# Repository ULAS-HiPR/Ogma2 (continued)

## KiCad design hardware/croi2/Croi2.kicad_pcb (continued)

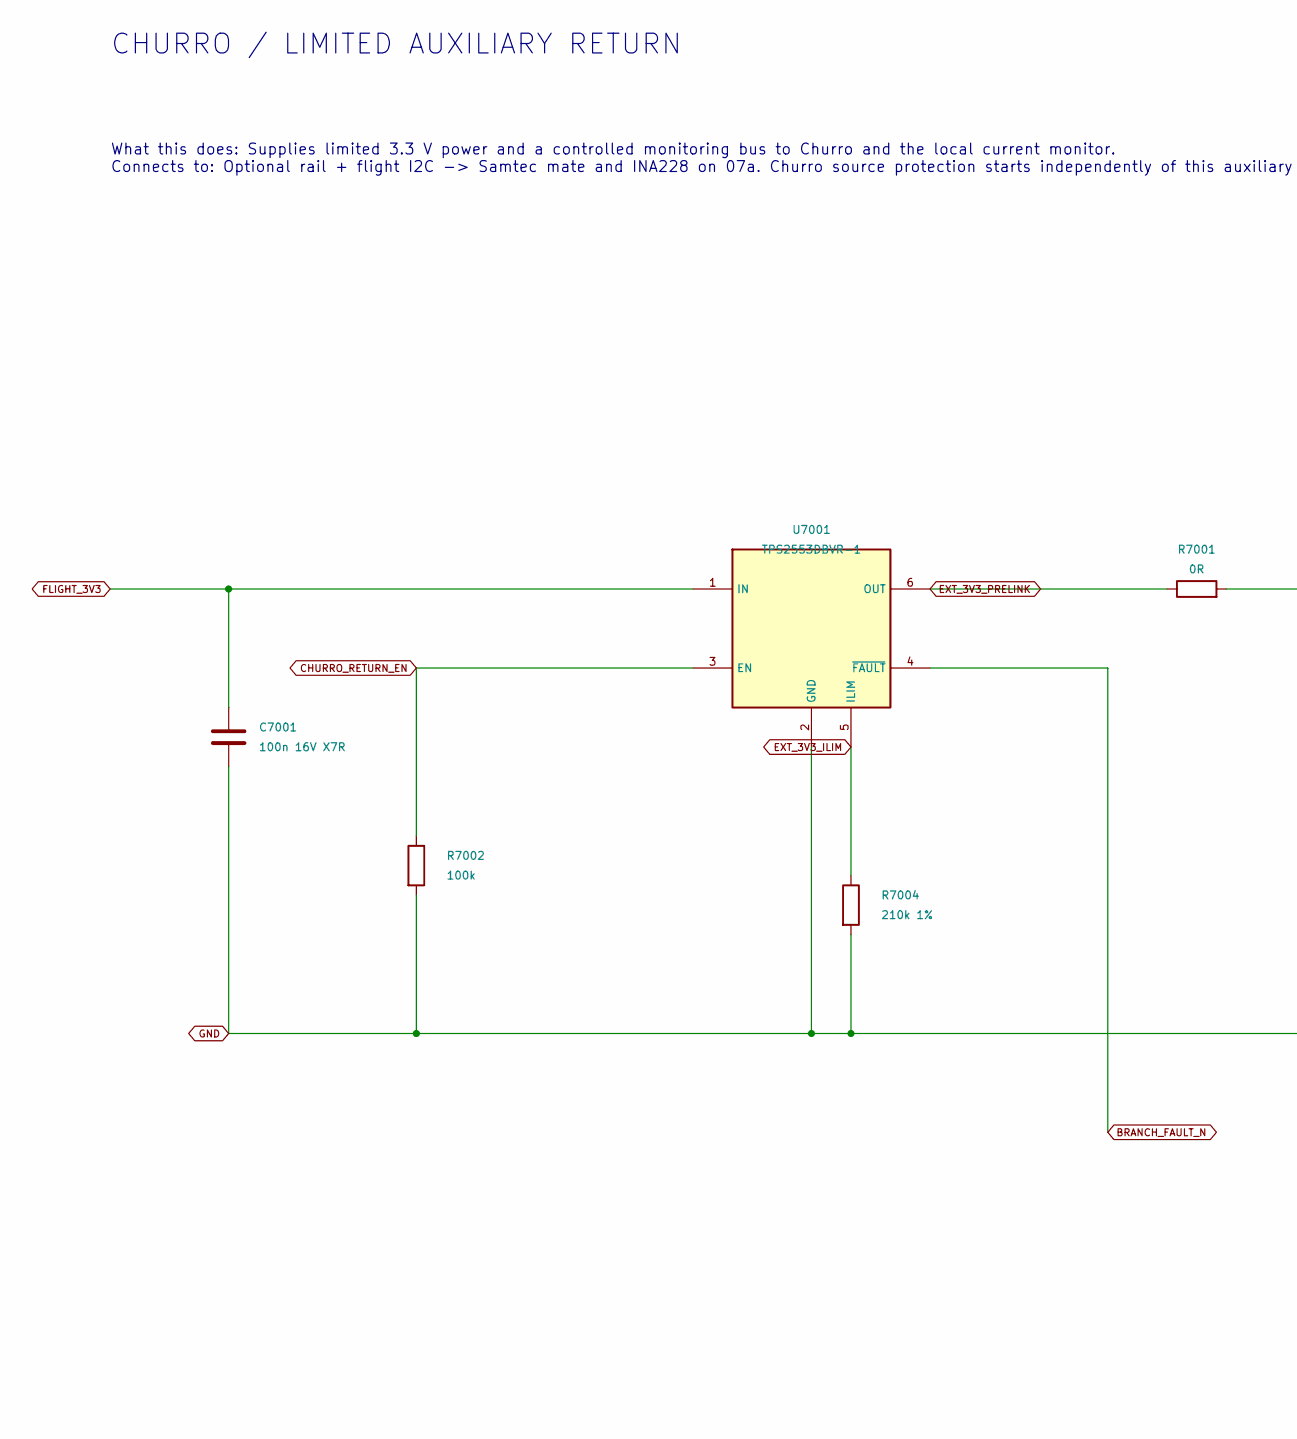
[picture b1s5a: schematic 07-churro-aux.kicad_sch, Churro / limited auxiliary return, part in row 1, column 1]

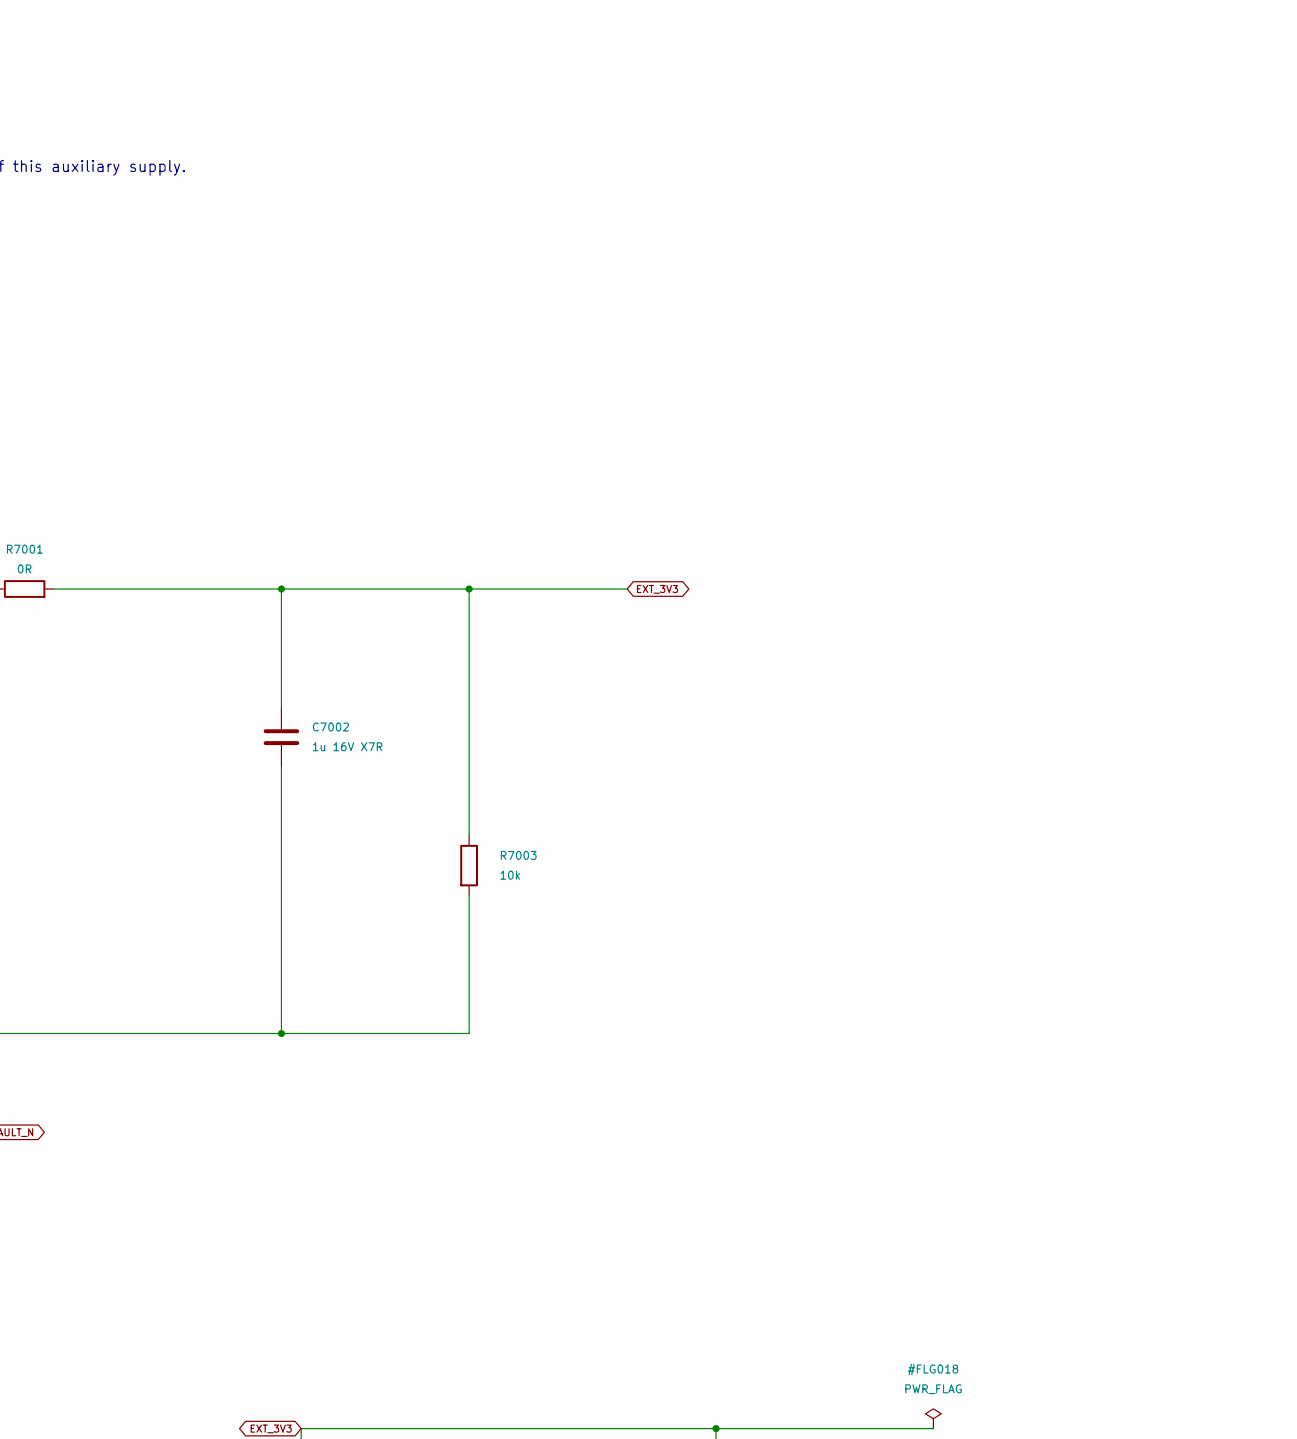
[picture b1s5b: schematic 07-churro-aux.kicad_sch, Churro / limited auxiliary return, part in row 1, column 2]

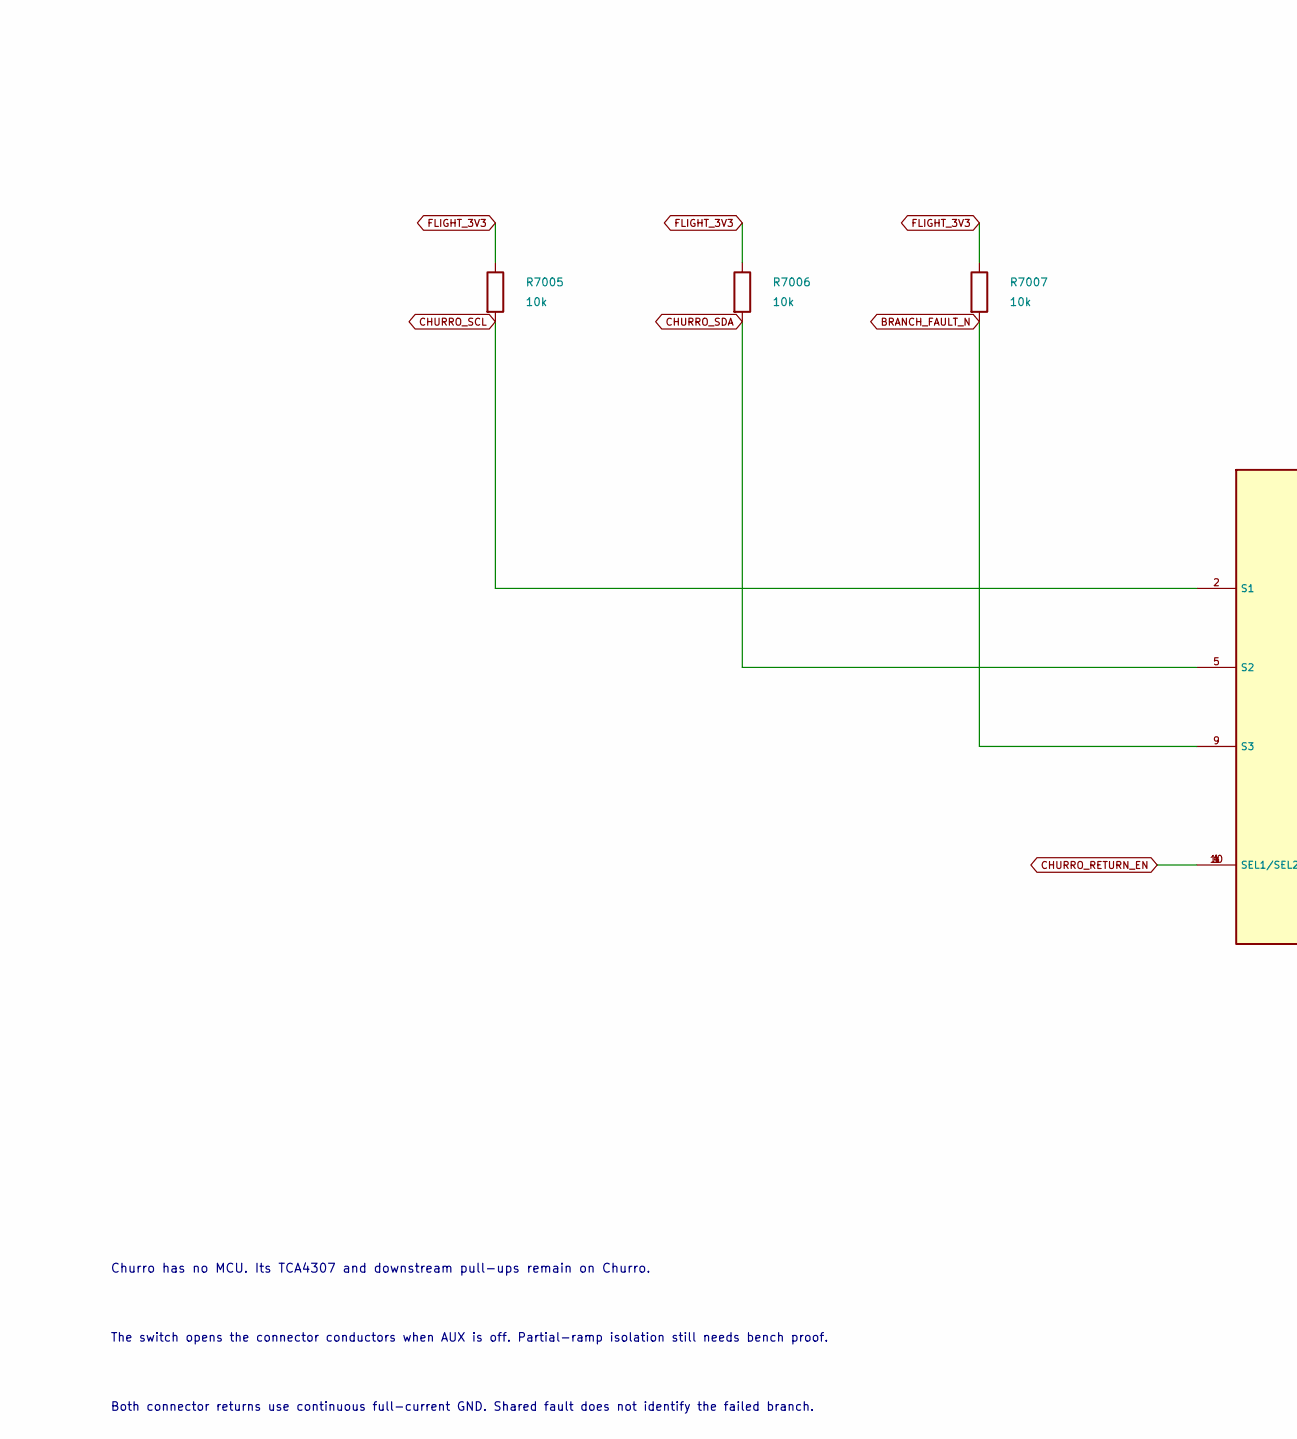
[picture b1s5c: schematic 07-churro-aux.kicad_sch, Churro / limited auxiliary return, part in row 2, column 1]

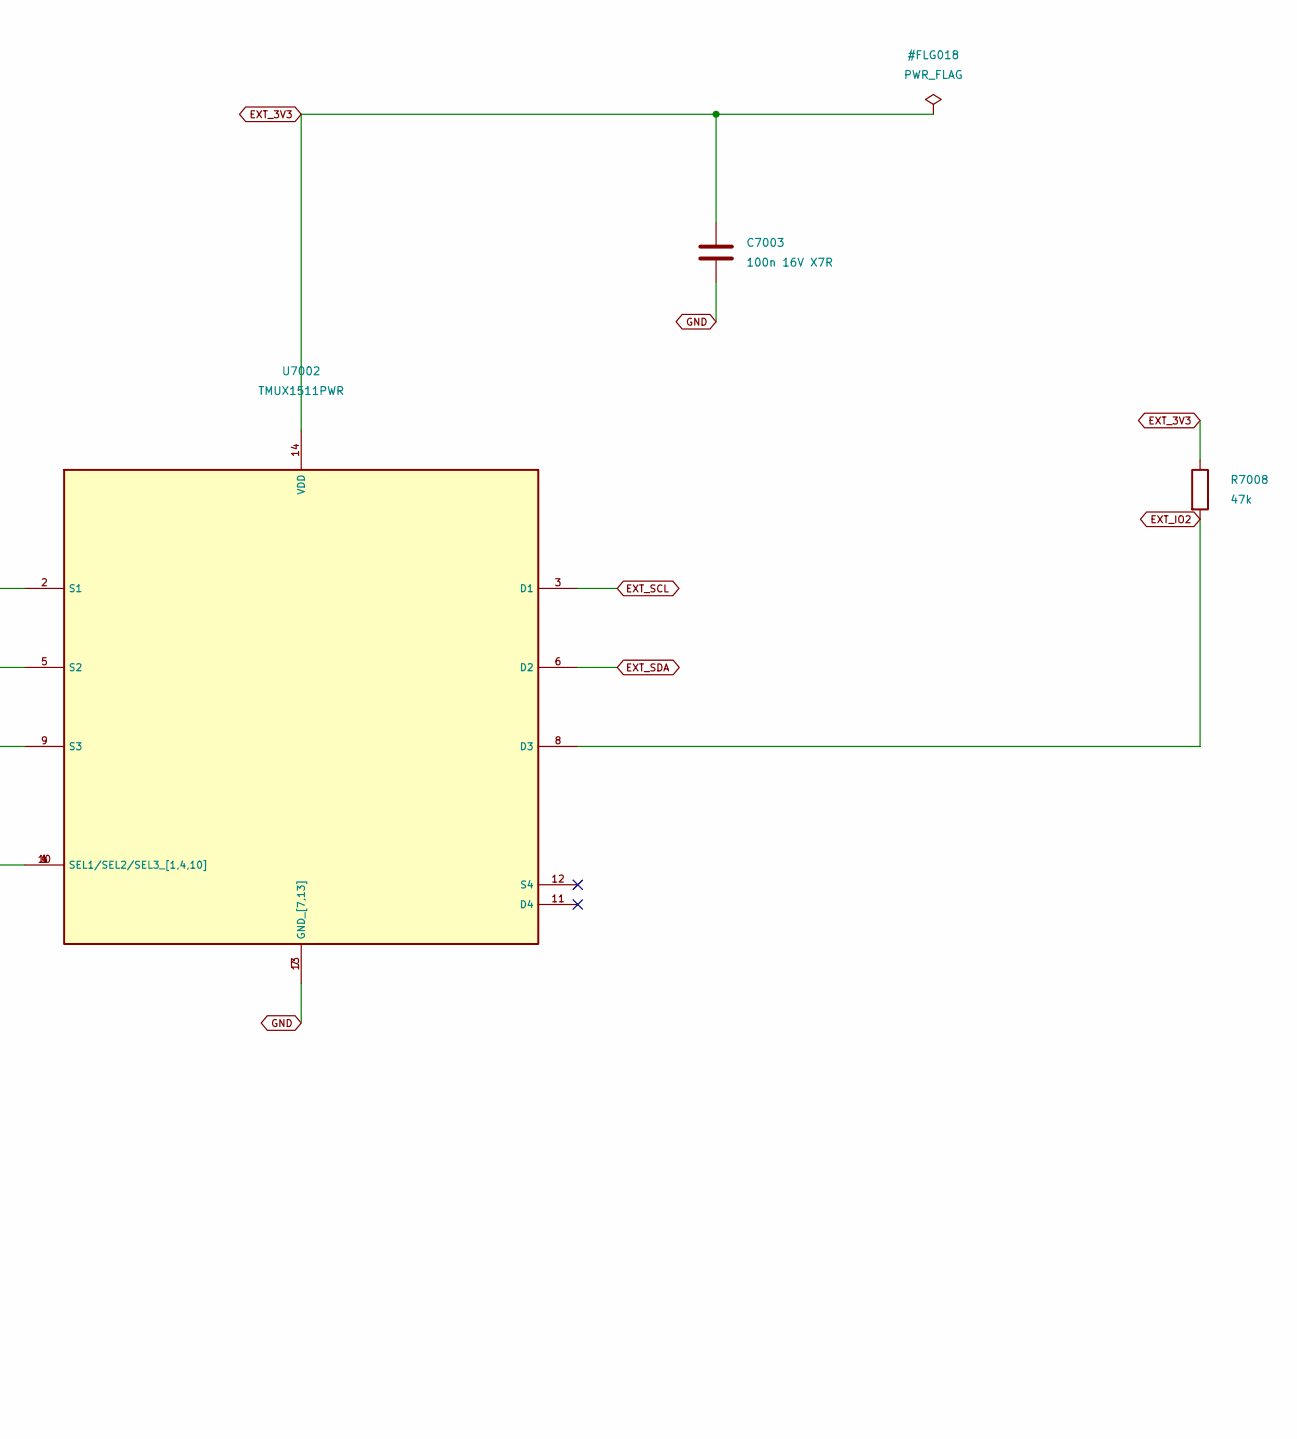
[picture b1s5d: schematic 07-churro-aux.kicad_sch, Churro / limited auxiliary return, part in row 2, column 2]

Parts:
C7001, C7003: 100n 16V X7R; C_0402_1005Metric; MPN CL05B104KB54PNC; LCSC C307331
C7002: 1u 16V X7R; C_0603_1608Metric
R7001: 0R; R_0603_1608Metric
R7002: 100k; R_0402_1005Metric; MPN 0402WGF1003TCE; LCSC C25741
R7003, R7005, R7006, R7007: 10k; R_0402_1005Metric; MPN 0402WGF1002TCE; LCSC C25744
R7004: 210k 1%; R_0603_1608Metric
R7008: 47k; R_0402_1005Metric; MPN 0402WGF4702TCE; LCSC C25792
U7001: TPS2553DBVR-1; MPN TPS2553DBVR-1
U7002: TMUX1511PWR; MPN TMUX1511PWR

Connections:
BRANCH_FAULT_N: R7007.2, U7001.4 (~FAULT), U7002.9 (S3); also elsewhere on the board
CHURRO_RETURN_EN: R7002.1, U7001.3 (EN), U7002.1 (SEL1/SEL2/SEL3_[1,4,10]), U7002.4, U7002.10; also elsewhere on the board
CHURRO_SCL: R7005.2, U7002.2 (S1); also elsewhere on the board
CHURRO_SDA: R7006.2, U7002.5 (S2); also elsewhere on the board
EXT_3V3: C7002.1, C7003.1, R7001.2, R7003.1, R7008.1, U7002.14 (VDD); also elsewhere on the board
EXT_3V3_ILIM: R7004.1, U7001.5 (ILIM)
EXT_3V3_PRELINK: R7001.1, U7001.6 (OUT)
EXT_IO2: R7008.2, U7002.8 (D3); also elsewhere on the board
EXT_SCL: U7002.3 (D1); also elsewhere on the board
EXT_SDA: U7002.6 (D2); also elsewhere on the board
FLIGHT_3V3: C7001.1, R7005.1, R7006.1, R7007.1, U7001.1 (IN); also elsewhere on the board
GND: C7001.2, C7002.2, C7003.2, R7002.2, R7003.2, R7004.2, U7001.2 (GND), U7002.7 (GND_[7,13]), U7002.13; also elsewhere on the board

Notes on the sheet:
Churro has no MCU. Its TCA4307 and downstream pull-ups remain on Churro.
CHURRO / LIMITED AUXILIARY RETURN
Both connector returns use continuous full-current GND. Shared fault does not identify the failed branch.
What this does: Supplies limited 3.3 V power and a controlled monitoring bus to Churro and the local current monitor. Connects to: Optional rail + flight I2C -> Samtec mate and INA228 on 07a. Churro source protection starts independently of this auxiliary supply.
The switch opens the connector conductors when AUX is off. Partial-ramp isolation still needs bench proof.

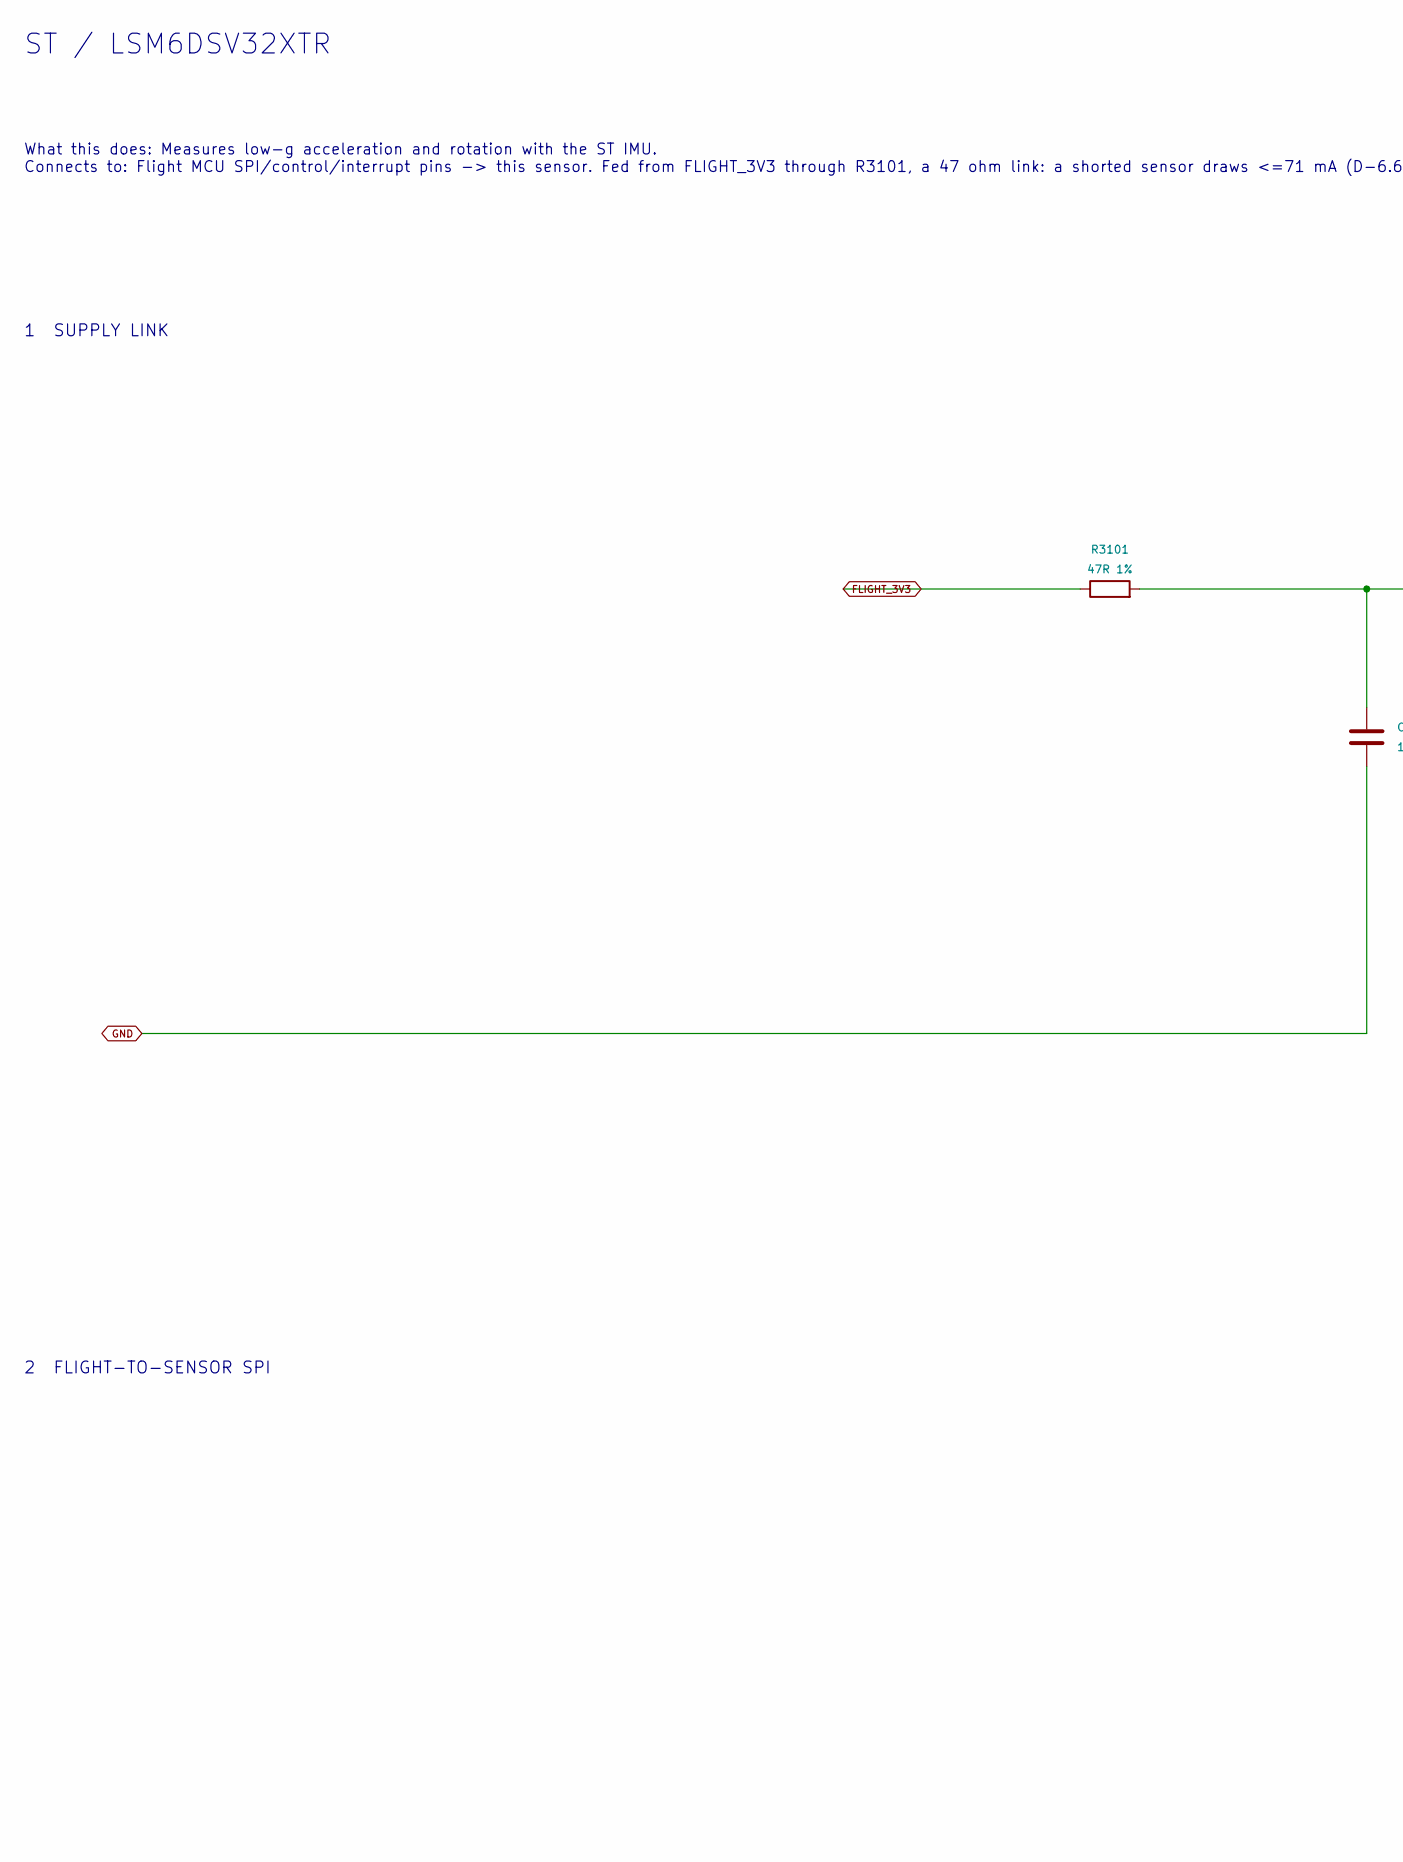
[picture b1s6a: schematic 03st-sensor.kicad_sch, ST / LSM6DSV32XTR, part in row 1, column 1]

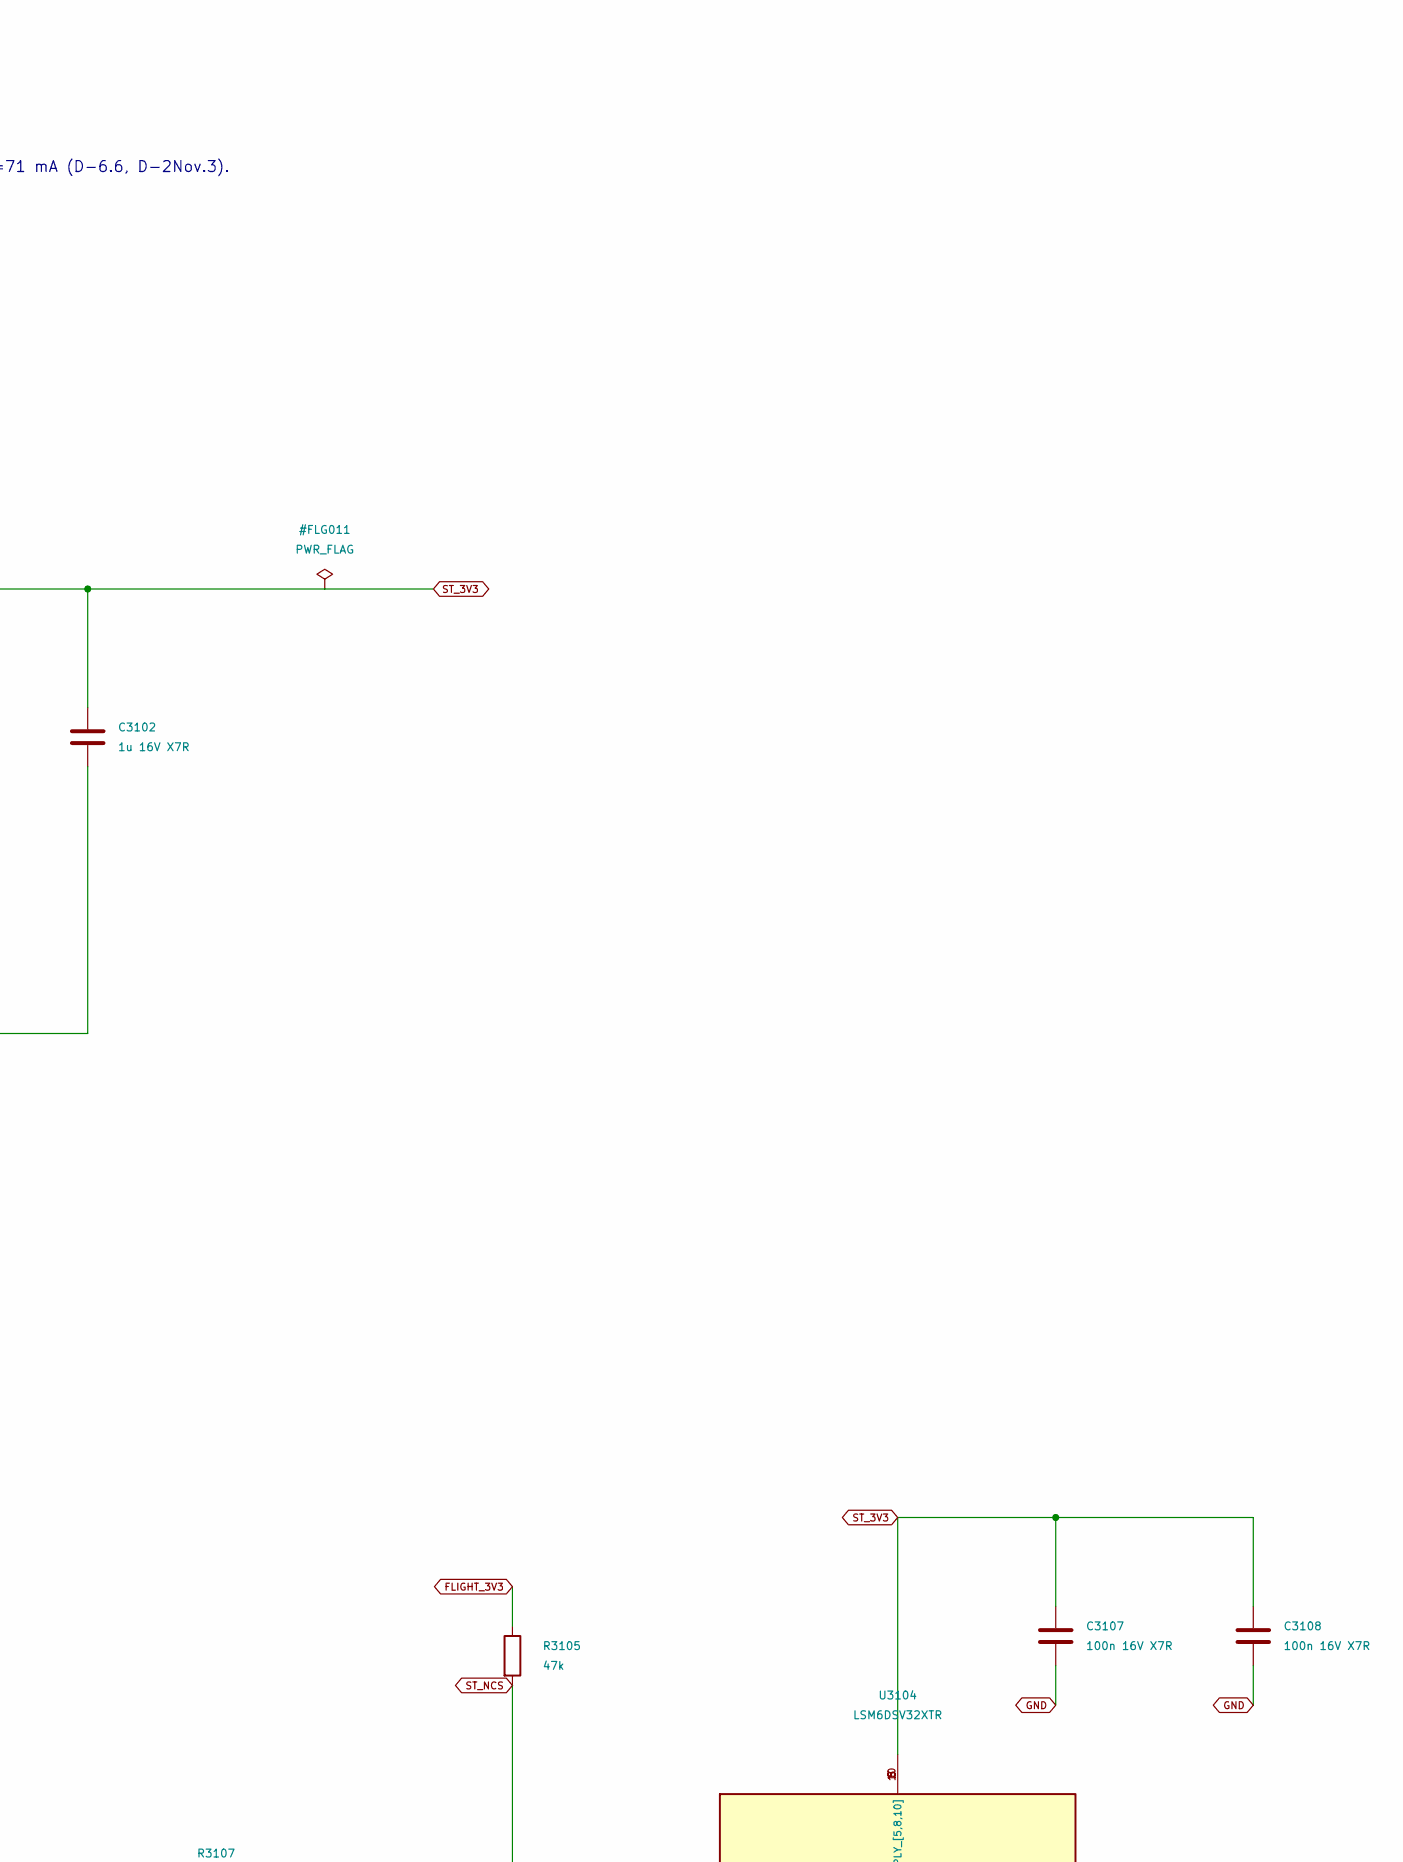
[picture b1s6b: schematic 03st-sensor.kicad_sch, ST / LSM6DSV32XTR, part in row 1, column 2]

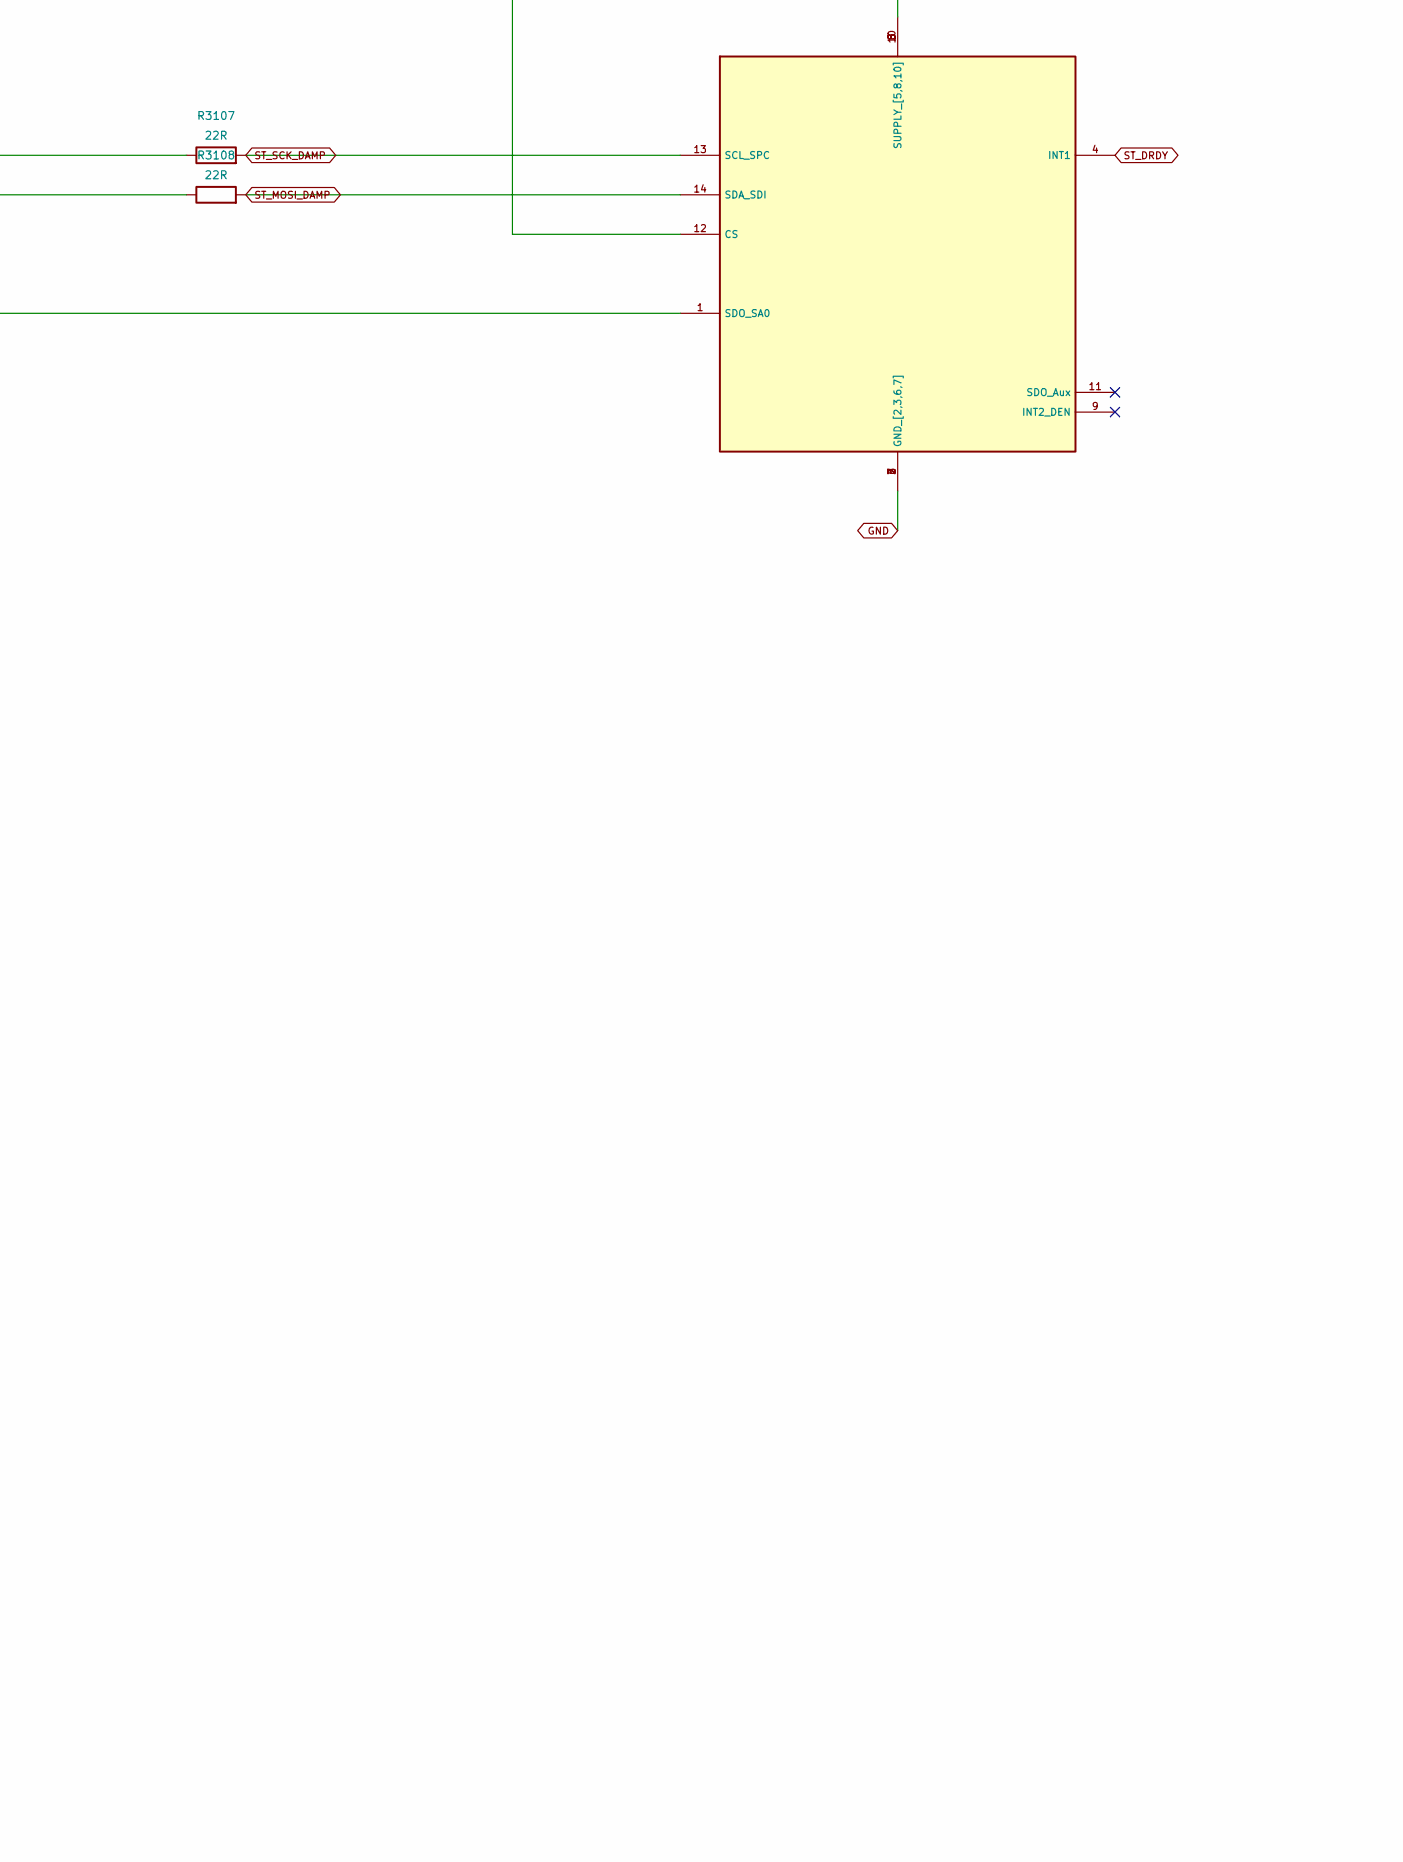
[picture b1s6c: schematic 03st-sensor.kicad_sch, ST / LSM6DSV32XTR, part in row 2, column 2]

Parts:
C3102: 1u 16V X7R; C_0603_1608Metric
C3107, C3108: 100n 16V X7R; C_0402_1005Metric; MPN CL05B104KB54PNC; LCSC C307331
R3101: 47R 1%; R_0402_1005Metric; MPN RC0402FR-0747RL; LCSC C137973
R3105: 47k; R_0402_1005Metric; MPN 0402WGF4702TCE; LCSC C25792
R3107, R3108: 22R; R_0402_1005Metric; MPN 0402WGF220JTCE; LCSC C25092
U3104: LSM6DSV32XTR; LSM6DSV16XTR; MPN LSM6DSV32XTR

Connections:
FLIGHT_3V3: R3101.1, R3105.1; also elsewhere on the board
GND: C3102.2, C3107.2, C3108.2, U3104.2 (GND_[2,3,6,7]), U3104.3, U3104.6, U3104.7; also elsewhere on the board
ST_3V3: C3102.1, C3107.1, C3108.1, R3101.2, U3104.5 (SUPPLY_[5,8,10]), U3104.8, U3104.10
ST_DRDY: U3104.4 (INT1); also elsewhere on the board
ST_MISO: U3104.1 (SDO_SA0); also elsewhere on the board
ST_MOSI: R3108.1; also elsewhere on the board
ST_MOSI_DAMP: R3108.2, U3104.14 (SDA_SDI)
ST_NCS: R3105.2, U3104.12 (CS); also elsewhere on the board
ST_SCK: R3107.1; also elsewhere on the board
ST_SCK_DAMP: R3107.2, U3104.13 (SCL_SPC)

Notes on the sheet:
What this does: Measures low-g acceleration and rotation with the ST IMU. Connects to: Flight MCU SPI/control/interrupt pins -> this sensor. Fed from FLIGHT_3V3 through R3101, a 47 ohm link: a shorted sensor draws <=71 mA (D-6.6, D-2Nov.3).
No switches or isolators (D-6.6). Firmware parks a dead sensor's bus pins so the MCU cannot back-power it through the 22 ohm damping (D-2Nov.3). Pull-ups go to FLIGHT_3V3.
2 FLIGHT-TO-SENSOR SPI
1 SUPPLY LINK
ST / LSM6DSV32XTR
